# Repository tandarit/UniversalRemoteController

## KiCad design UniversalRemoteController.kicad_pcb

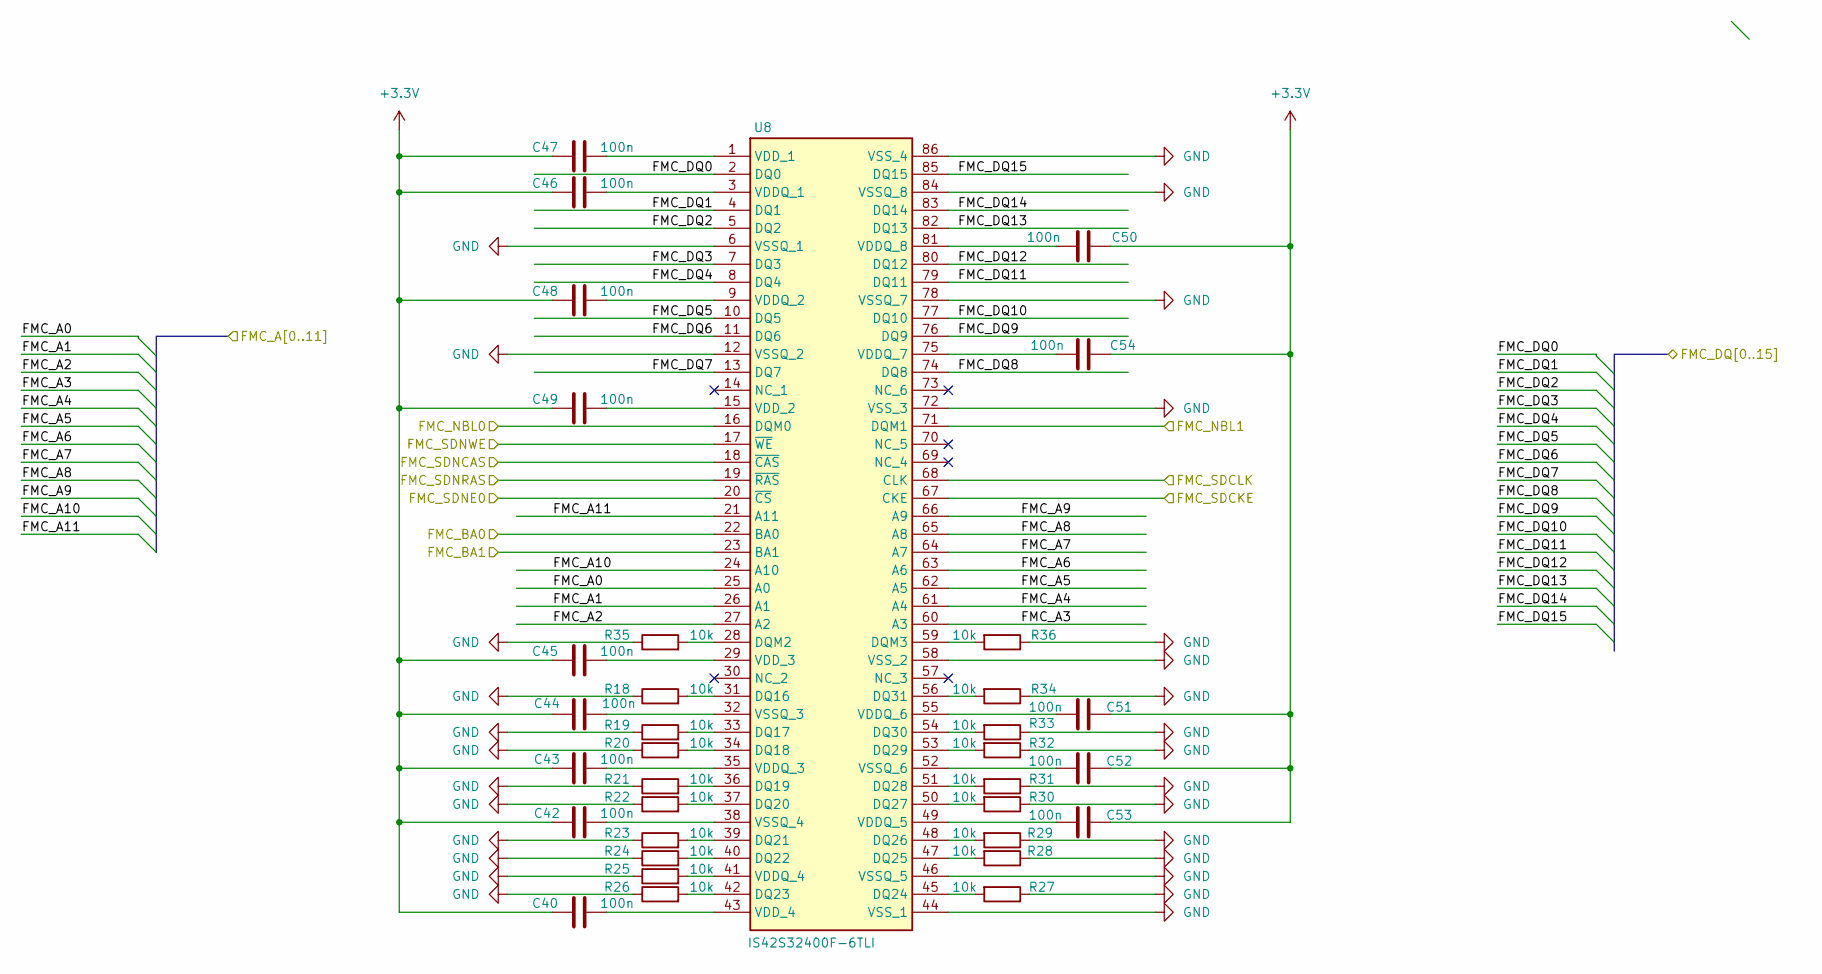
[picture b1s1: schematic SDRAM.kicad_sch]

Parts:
C40, C42, C43, C44, C45, C46, C47, C48, C49, C50, C51, C52, C53, C54: 100n; C_0402_1005Metric
R18, R19, R20, R21, R22, R23, R24, R25, R26, R27, R28, R29, R30, R31, R32, R33, R34, R35, R36: 10k; C_0402_1005Metric
U8: IS42S32400F-6TLI; SOP50P1176X120-86N; Mouser Part Number 870-IS42S32400F-6TLI

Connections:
+3.3V: C40.1, C42.1, C43.1, C44.1, C45.1, C46.1, C47.1, C48.1, C49.1, C50.1, C51.1, C52.1, C53.1, C54.1; also elsewhere on the board
/MCU/FMC_A0: U8.25 (A0); also elsewhere on the board
/MCU/FMC_A1: U8.26 (A1); also elsewhere on the board
/MCU/FMC_A2: U8.27 (A2); also elsewhere on the board
/MCU/FMC_A3: U8.60 (A3); also elsewhere on the board
/MCU/FMC_A4: U8.61 (A4); also elsewhere on the board
/MCU/FMC_A5: U8.62 (A5); also elsewhere on the board
/MCU/FMC_A6: U8.63 (A6); also elsewhere on the board
/MCU/FMC_A7: U8.64 (A7); also elsewhere on the board
/MCU/FMC_A8: U8.65 (A8); also elsewhere on the board
/MCU/FMC_A9: U8.66 (A9); also elsewhere on the board
/MCU/FMC_A10: U8.24 (A10); also elsewhere on the board
/MCU/FMC_A11: U8.21 (A11); also elsewhere on the board
/MCU/FMC_BA0: U8.22 (BA0); also elsewhere on the board
/MCU/FMC_BA1: U8.23 (BA1); also elsewhere on the board
/MCU/FMC_DQ0: U8.2 (DQ0); also elsewhere on the board
/MCU/FMC_DQ1: U8.4 (DQ1); also elsewhere on the board
/MCU/FMC_DQ2: U8.5 (DQ2); also elsewhere on the board
/MCU/FMC_DQ3: U8.7 (DQ3); also elsewhere on the board
/MCU/FMC_DQ4: U8.8 (DQ4); also elsewhere on the board
/MCU/FMC_DQ5: U8.10 (DQ5); also elsewhere on the board
/MCU/FMC_DQ6: U8.11 (DQ6); also elsewhere on the board
/MCU/FMC_DQ7: U8.13 (DQ7); also elsewhere on the board
/MCU/FMC_DQ8: U8.74 (DQ8); also elsewhere on the board
/MCU/FMC_DQ9: U8.76 (DQ9); also elsewhere on the board
/MCU/FMC_DQ10: U8.77 (DQ10); also elsewhere on the board
/MCU/FMC_DQ11: U8.79 (DQ11); also elsewhere on the board
/MCU/FMC_DQ12: U8.80 (DQ12); also elsewhere on the board
/MCU/FMC_DQ13: U8.82 (DQ13); also elsewhere on the board
/MCU/FMC_DQ14: U8.83 (DQ14); also elsewhere on the board
/MCU/FMC_DQ15: U8.85 (DQ15); also elsewhere on the board
/MCU/FMC_NBL0: U8.16 (DQM0); also elsewhere on the board
/MCU/FMC_NBL1: U8.71 (DQM1); also elsewhere on the board
/MCU/FMC_SDCKE: U8.67 (CKE); also elsewhere on the board
/MCU/FMC_SDCLK: U8.68 (CLK); also elsewhere on the board
/MCU/FMC_SDNCAS: U8.18 (~CAS); also elsewhere on the board
/MCU/FMC_SDNE0: U8.20 (~CS); also elsewhere on the board
/MCU/FMC_SDNRAS: U8.19 (~RAS); also elsewhere on the board
/MCU/FMC_SDNWE: U8.17 (~WE); also elsewhere on the board
GND: R18.1, R19.1, R20.1, R21.1, R22.1, R23.1, R24.1, R25.1, R26.1, R27.1, R28.1, R29.1, R30.1, R31.1, R32.1, R33.1, R34.1, R35.1, R36.1, U8.6 (VSSQ_1), U8.12 (VSSQ_2), U8.44 (VSS_1), U8.46 (VSSQ_5), U8.58 (VSS_2), U8.72 (VSS_3), U8.78 (VSSQ_7), U8.84 (VSSQ_8), U8.86 (VSS_4); also elsewhere on the board
unnamed: R18.2, U8.31 (DQ16)
unnamed: R19.2, U8.33 (DQ17)
unnamed: R20.2, U8.34 (DQ18)
unnamed: R21.2, U8.36 (DQ19)
unnamed: R22.2, U8.37 (DQ20)
unnamed: R23.2, U8.39 (DQ21)
unnamed: R24.2, U8.40 (DQ22)
unnamed: R26.2, U8.42 (DQ23)
unnamed: R27.2, U8.45 (DQ24)
unnamed: R28.2, U8.47 (DQ25)
unnamed: R29.2, U8.48 (DQ26)
unnamed: R30.2, U8.50 (DQ27)
unnamed: R31.2, U8.51 (DQ28)
unnamed: R32.2, U8.53 (DQ29)
unnamed: R33.2, U8.54 (DQ30)
unnamed: R34.2, U8.56 (DQ31)
unnamed: R35.2, U8.28 (DQM2)
unnamed: R36.2, U8.59 (DQM3)
unnamed: C46.2, U8.3 (VDDQ_1)
unnamed: C48.2, U8.9 (VDDQ_2)
unnamed: C43.2, U8.35 (VDDQ_3)
unnamed: R25.2, U8.41 (VDDQ_4)
unnamed: C53.2, U8.49 (VDDQ_5)
unnamed: C51.2, U8.55 (VDDQ_6)
unnamed: C54.2, U8.75 (VDDQ_7)
unnamed: C50.2, U8.81 (VDDQ_8)
unnamed: C47.2, U8.1 (VDD_1)
unnamed: C49.2, U8.15 (VDD_2)
unnamed: C45.2, U8.29 (VDD_3)
unnamed: C40.2, U8.43 (VDD_4)
unnamed: C44.2, U8.32 (VSSQ_3)
unnamed: C42.2, U8.38 (VSSQ_4)
unnamed: C52.2, U8.52 (VSSQ_6)

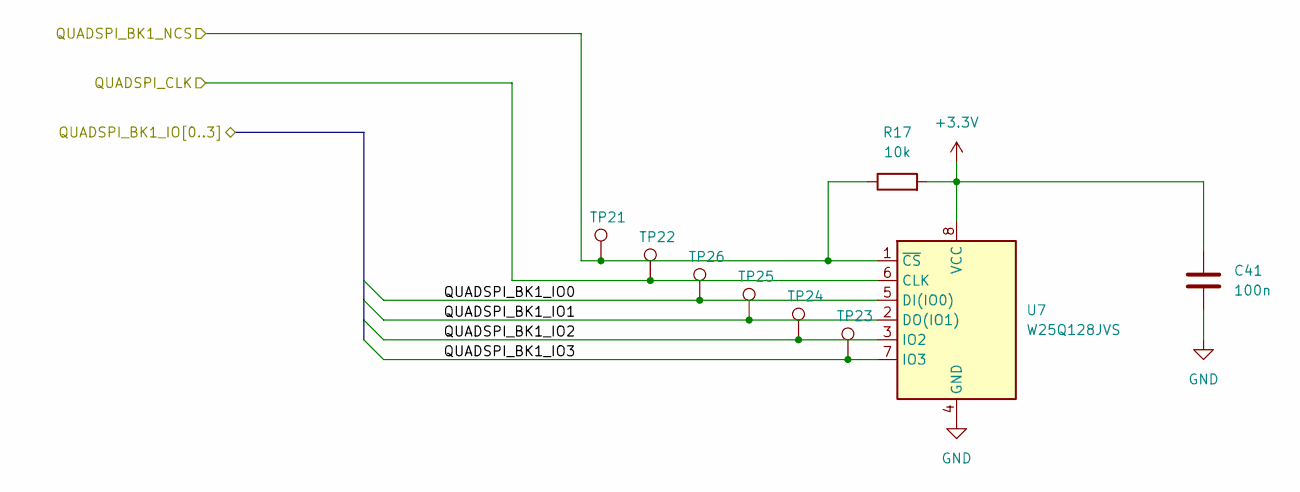
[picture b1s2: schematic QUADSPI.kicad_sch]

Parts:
C41: 100n; C_0402_1005Metric
R17: 10k; R_0402_1005Metric
TP21, TP22, TP23, TP24, TP25, TP26: TestPoint; TestPoint_Pad_D1.0mm
U7: W25Q128JVS; SOIC-8_5.23x5.23mm_P1.27mm

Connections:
+3.3V: C41.1, R17.2, U7.8 (VCC); also elsewhere on the board
/MCU/QUADSPI_BK1_IO0: TP26.1, U7.5 (DI(IO0)); also elsewhere on the board
/MCU/QUADSPI_BK1_IO1: TP25.1, U7.2 (DO(IO1)); also elsewhere on the board
/MCU/QUADSPI_BK1_IO2: TP24.1, U7.3 (IO2); also elsewhere on the board
/MCU/QUADSPI_BK1_IO3: TP23.1, U7.7 (IO3); also elsewhere on the board
/MCU/QUADSPI_BK1_NCS: TP22.1, U7.6 (CLK); also elsewhere on the board
/MCU/QUADSPI_CLK: R17.1, TP21.1, U7.1 (~CS); also elsewhere on the board
GND: C41.2, U7.4 (GND); also elsewhere on the board

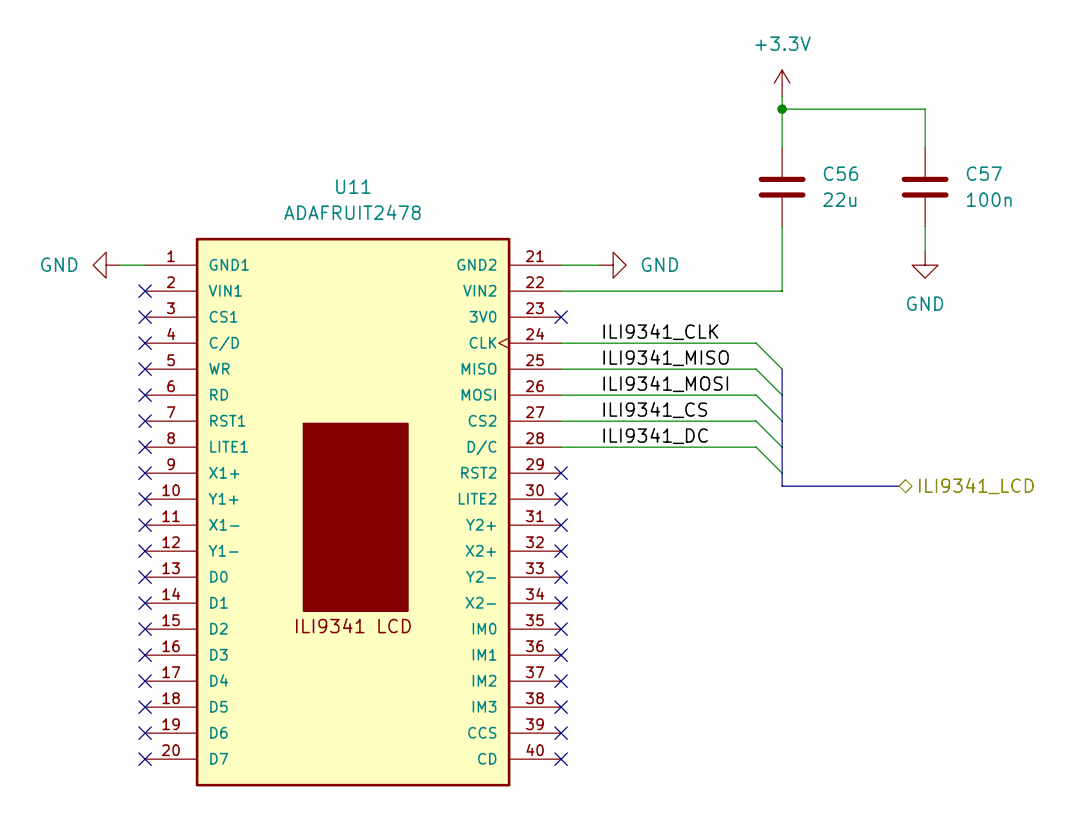
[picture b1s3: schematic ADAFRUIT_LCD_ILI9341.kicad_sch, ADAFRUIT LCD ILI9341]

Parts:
C56: 22u; C_0805_2012Metric
C57: 100n; C_0402_1005Metric
U11: ADAFRUIT2478; ADAFRUIT_2478

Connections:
+3.3V: C56.1, C57.1; also elsewhere on the board
/ADAFRUIT_LCD_ILI9341/ILI9341_CLK: U11.24 (CLK)
/ADAFRUIT_LCD_ILI9341/ILI9341_CS: U11.27 (CS2)
/ADAFRUIT_LCD_ILI9341/ILI9341_DC: U11.28 (D/C)
/ADAFRUIT_LCD_ILI9341/ILI9341_MISO: U11.25 (MISO)
/ADAFRUIT_LCD_ILI9341/ILI9341_MOSI: U11.26 (MOSI)
GND: C57.2, U11.1 (GND1), U11.21 (GND2); also elsewhere on the board
unnamed: C56.2, U11.22 (VIN2)

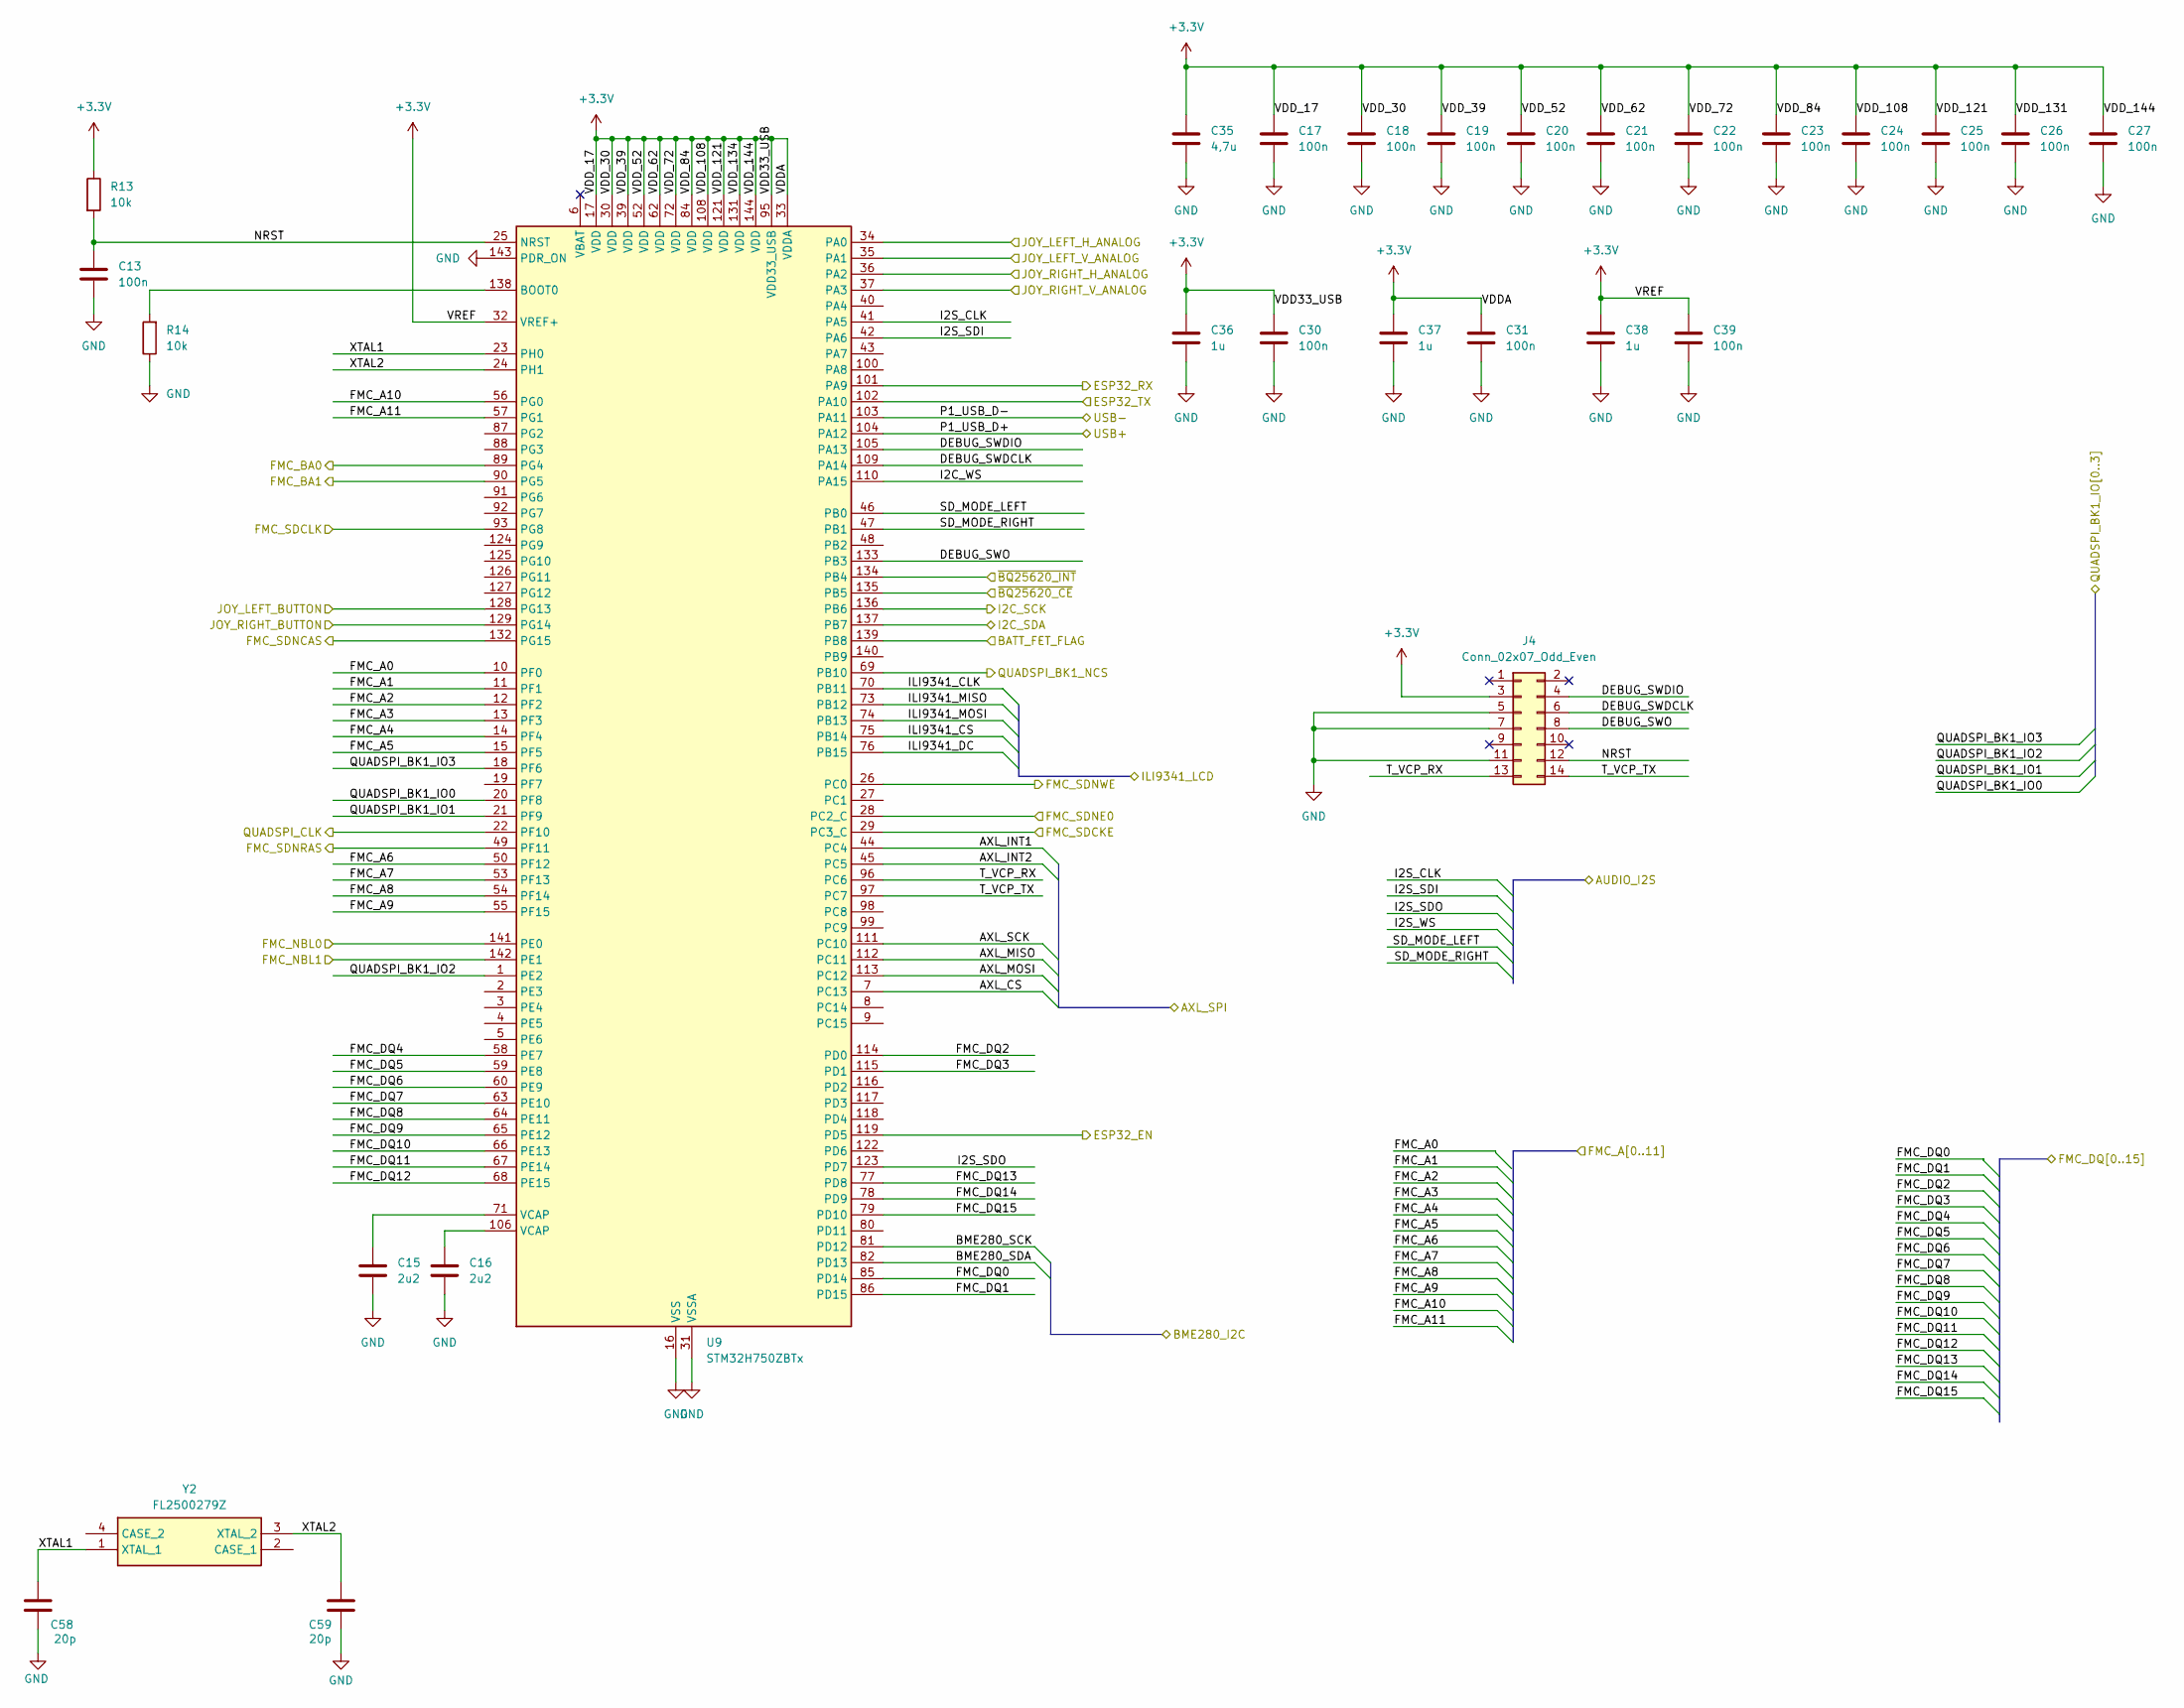
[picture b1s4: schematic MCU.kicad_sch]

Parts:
C13, C17, C18, C19, C20, C21, C22, C23, C24, C25, C26, C27, C30, C31, C39: 100n; C_0402_1005Metric
C15, C16: 2u2; C_0805_2012Metric
C35: 4,7u; C_0603_1608Metric
C36, C37, C38: 1u; C_0603_1608Metric
C58, C59: 20p; C_0402_1005Metric
J4: Conn_02x07_Odd_Even; PinHeader_2x07_P1.27mm_Vertical_SMD
R13, R14: 10k; C_0805_2012Metric
U9: STM32H750ZBTx; LQFP-144_20x20mm_P0.5mm
Y2: FL2500279Z; Mouser Part Number 729-FL2500279Z

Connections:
+3.3V: C17.1, C18.1, C19.1, C20.1, C21.1, C22.1, C23.1, C24.1, C25.1, C26.1, C27.1, C30.1, C31.1, C35.1, C36.1, C37.1, C38.1, C39.1, J4.3, R13.1, U9.17 (VDD), U9.30 (VDD), U9.32 (VREF+), U9.33 (VDDA), U9.39 (VDD), U9.52 (VDD), U9.62 (VDD), U9.72 (VDD), U9.84 (VDD), U9.95 (VDD33_USB), U9.108 (VDD), U9.121 (VDD), U9.131 (VDD), U9.144 (VDD); also elsewhere on the board
/BluetoothWiFi/ESP32_EN: U9.119 (PD5); also elsewhere on the board
/BluetoothWiFi/ESP32_RX: U9.101 (PA9); also elsewhere on the board
/BluetoothWiFi/ESP32_TX: U9.102 (PA10); also elsewhere on the board
/MCU/AXL_CS: U9.7 (PC13)
/MCU/AXL_INT1: U9.44 (PC4)
/MCU/AXL_INT2: U9.45 (PC5)
/MCU/AXL_MISO: U9.112 (PC11)
/MCU/AXL_MOSI: U9.113 (PC12)
/MCU/AXL_SCK: U9.111 (PC10)
/MCU/BATT_FET_FLAG: U9.139 (PB8); also elsewhere on the board
/MCU/BME280_SCK: U9.81 (PD12)
/MCU/BME280_SDA: U9.82 (PD13)
/MCU/DEBUG_SWDCLK: J4.6, U9.109 (PA14)
/MCU/DEBUG_SWDIO: J4.4, U9.105 (PA13)
/MCU/DEBUG_SWO: J4.8, U9.133 (PB3)
/MCU/FMC_A0: U9.10 (PF0); also elsewhere on the board
/MCU/FMC_A1: U9.11 (PF1); also elsewhere on the board
/MCU/FMC_A2: U9.12 (PF2); also elsewhere on the board
/MCU/FMC_A3: U9.13 (PF3); also elsewhere on the board
/MCU/FMC_A4: U9.14 (PF4); also elsewhere on the board
/MCU/FMC_A5: U9.15 (PF5); also elsewhere on the board
/MCU/FMC_A6: U9.50 (PF12); also elsewhere on the board
/MCU/FMC_A7: U9.53 (PF13); also elsewhere on the board
/MCU/FMC_A8: U9.54 (PF14); also elsewhere on the board
/MCU/FMC_A9: U9.55 (PF15); also elsewhere on the board
/MCU/FMC_A10: U9.56 (PG0); also elsewhere on the board
/MCU/FMC_A11: U9.57 (PG1); also elsewhere on the board
/MCU/FMC_BA0: U9.89 (PG4); also elsewhere on the board
/MCU/FMC_BA1: U9.90 (PG5); also elsewhere on the board
/MCU/FMC_DQ0: U9.85 (PD14); also elsewhere on the board
/MCU/FMC_DQ1: U9.86 (PD15); also elsewhere on the board
/MCU/FMC_DQ2: U9.114 (PD0); also elsewhere on the board
/MCU/FMC_DQ3: U9.115 (PD1); also elsewhere on the board
/MCU/FMC_DQ4: U9.58 (PE7); also elsewhere on the board
/MCU/FMC_DQ5: U9.59 (PE8); also elsewhere on the board
/MCU/FMC_DQ6: U9.60 (PE9); also elsewhere on the board
/MCU/FMC_DQ7: U9.63 (PE10); also elsewhere on the board
/MCU/FMC_DQ8: U9.64 (PE11); also elsewhere on the board
/MCU/FMC_DQ9: U9.65 (PE12); also elsewhere on the board
/MCU/FMC_DQ10: U9.66 (PE13); also elsewhere on the board
/MCU/FMC_DQ11: U9.67 (PE14); also elsewhere on the board
/MCU/FMC_DQ12: U9.68 (PE15); also elsewhere on the board
/MCU/FMC_DQ13: U9.77 (PD8); also elsewhere on the board
/MCU/FMC_DQ14: U9.78 (PD9); also elsewhere on the board
/MCU/FMC_DQ15: U9.79 (PD10); also elsewhere on the board
/MCU/FMC_NBL0: U9.141 (PE0); also elsewhere on the board
/MCU/FMC_NBL1: U9.142 (PE1); also elsewhere on the board
/MCU/FMC_SDCKE: U9.29 (PC3_C); also elsewhere on the board
/MCU/FMC_SDCLK: U9.93 (PG8); also elsewhere on the board
/MCU/FMC_SDNCAS: U9.132 (PG15); also elsewhere on the board
/MCU/FMC_SDNE0: U9.28 (PC2_C); also elsewhere on the board
/MCU/FMC_SDNRAS: U9.49 (PF11); also elsewhere on the board
/MCU/FMC_SDNWE: U9.26 (PC0); also elsewhere on the board
/MCU/I2C_SCK: U9.136 (PB6); also elsewhere on the board
/MCU/I2C_SDA: U9.137 (PB7); also elsewhere on the board
/MCU/I2C_WS: U9.110 (PA15)
/MCU/I2S_CLK: U9.41 (PA5)
/MCU/I2S_SDI: U9.42 (PA6)
/MCU/I2S_SDO: U9.123 (PD7)
/MCU/ILI9341_CLK: U9.70 (PB11)
/MCU/ILI9341_CS: U9.75 (PB14)
/MCU/ILI9341_DC: U9.76 (PB15)
/MCU/ILI9341_MISO: U9.73 (PB12)
/MCU/ILI9341_MOSI: U9.74 (PB13)
/MCU/JOY_LEFT_BUTTON: U9.128 (PG13); also elsewhere on the board
/MCU/JOY_LEFT_H_ANALOG: U9.34 (PA0); also elsewhere on the board
/MCU/JOY_LEFT_V_ANALOG: U9.35 (PA1); also elsewhere on the board
/MCU/JOY_RIGHT_BUTTON: U9.129 (PG14); also elsewhere on the board
/MCU/JOY_RIGHT_H_ANALOG: U9.36 (PA2); also elsewhere on the board
/MCU/JOY_RIGHT_V_ANALOG: U9.37 (PA3); also elsewhere on the board
/MCU/NRST: C13.1, J4.12, R13.2, U9.25 (NRST)
/MCU/P1_USB_D+: U9.104 (PA12); also elsewhere on the board
/MCU/P1_USB_D-: U9.103 (PA11); also elsewhere on the board
/MCU/QUADSPI_BK1_IO0: U9.20 (PF8); also elsewhere on the board
/MCU/QUADSPI_BK1_IO1: U9.21 (PF9); also elsewhere on the board
/MCU/QUADSPI_BK1_IO2: U9.1 (PE2); also elsewhere on the board
/MCU/QUADSPI_BK1_IO3: U9.18 (PF6); also elsewhere on the board
/MCU/QUADSPI_BK1_NCS: U9.69 (PB10); also elsewhere on the board
/MCU/QUADSPI_CLK: U9.22 (PF10); also elsewhere on the board
/MCU/SD_MODE_LEFT: U9.46 (PB0)
/MCU/SD_MODE_RIGHT: U9.47 (PB1)
/MCU/T_VCP_RX: J4.13, U9.96 (PC6)
/MCU/T_VCP_TX: J4.14, U9.97 (PC7)
/MCU/XTAL1: C58.1, U9.23 (PH0), Y2.1 (XTAL_1)
/MCU/XTAL2: C59.1, U9.24 (PH1), Y2.3 (XTAL_2)
/MCU/~BQ25620_CE: U9.135 (PB5); also elsewhere on the board
/MCU/~BQ25620_INT: U9.134 (PB4); also elsewhere on the board
GND: C13.2, C15.1, C16.1, C17.2, C18.2, C19.2, C20.2, C21.2, C22.2, C23.2, C24.2, C25.2, C26.2, C27.2, C30.2, C31.2, C35.2, C36.2, C37.2, C38.2, C39.2, C58.2, C59.2, J4.5, J4.7, J4.11, R14.1, U9.16 (VSS), U9.31 (VSSA), U9.38 (VSS), U9.51 (VSS), U9.61 (VSS), U9.83 (VSS), U9.94 (VSS), U9.107 (VSS), U9.120 (VSS), U9.130 (VSS), U9.143 (PDR_ON); also elsewhere on the board
unnamed: C15.2, U9.71 (VCAP)
unnamed: C16.2, U9.106 (VCAP)
unnamed: R14.2, U9.138 (BOOT0)

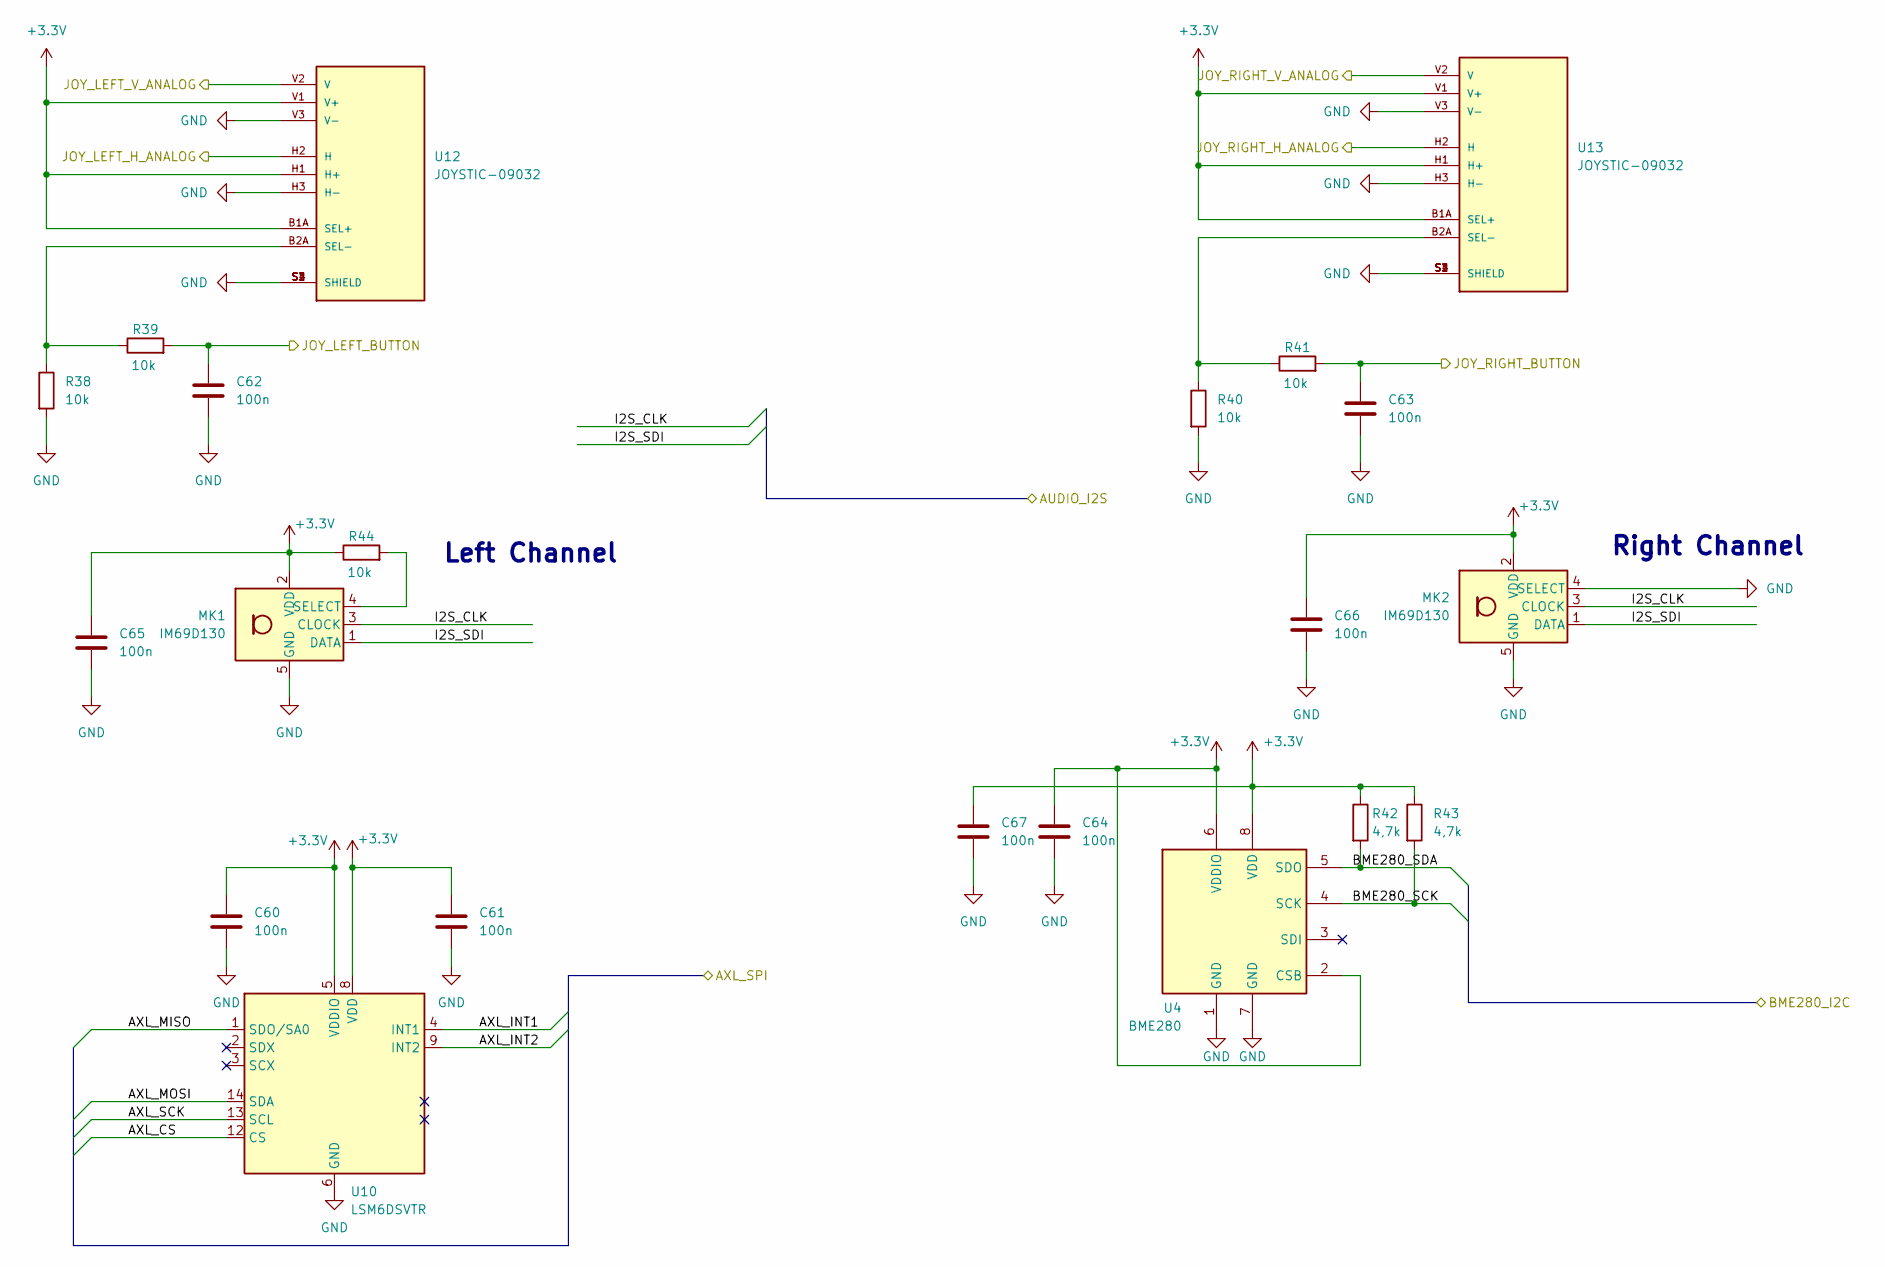
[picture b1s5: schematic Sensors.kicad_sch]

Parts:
C60, C61, C62, C63, C64, C65, C66, C67: 100n; C_0402_1005Metric
MK1, MK2: IM69D130; Infineon_PG-LLGA-5-1
R38, R39, R40, R41: 10k; C_0402_1005Metric
R42, R43: 4,7k; C_0402_1005Metric
R44: 10k; R_0402_1005Metric
U4: BME280; Bosch_LGA-8_2.5x2.5mm_P0.65mm_ClockwisePinNumbering
U10: LSM6DSVTR; LGA-14_3x2.5mm_P0.5mm_LayoutBorder3x4y
U12, U13: JOYSTIC-09032; XDCR_COM-09032; PARTREV N/A

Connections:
+3.3V: C60.1, C61.1, C64.1, C65.1, C66.1, C67.1, MK1.2 (VDD), MK2.2 (VDD), R42.1, R43.1, R44.1, U4.2 (CSB), U4.6 (VDDIO), U4.8 (VDD), U10.5 (VDDIO), U10.8 (VDD), U12.B1A (SEL+), U12.H1 (H+), U12.V1 (V+), U13.B1A (SEL+), U13.H1 (H+), U13.V1 (V+); also elsewhere on the board
/MCU/JOY_LEFT_BUTTON: C62.1, R39.2; also elsewhere on the board
/MCU/JOY_LEFT_H_ANALOG: U12.H2 (H); also elsewhere on the board
/MCU/JOY_LEFT_V_ANALOG: U12.V2 (V); also elsewhere on the board
/MCU/JOY_RIGHT_BUTTON: C63.1, R41.2; also elsewhere on the board
/MCU/JOY_RIGHT_H_ANALOG: U13.H2 (H); also elsewhere on the board
/MCU/JOY_RIGHT_V_ANALOG: U13.V2 (V); also elsewhere on the board
/Sensors/AXL_CS: U10.12 (CS)
/Sensors/AXL_INT1: U10.4 (INT1)
/Sensors/AXL_INT2: U10.9 (INT2)
/Sensors/AXL_MISO: U10.1 (SDO/SA0)
/Sensors/AXL_MOSI: U10.14 (SDA)
/Sensors/AXL_SCK: U10.13 (SCL)
/Sensors/BME280_SCK: R43.2, U4.4 (SCK)
/Sensors/BME280_SDA: R42.2, U4.5 (SDO)
/Sensors/I2S_CLK: MK1.3 (CLOCK), MK2.3 (CLOCK)
/Sensors/I2S_SDI: MK1.1 (DATA), MK2.1 (DATA)
GND: C60.2, C61.2, C62.2, C63.2, C64.2, C65.2, C66.2, C67.2, MK1.5 (GND), MK2.4 (SELECT), MK2.5 (GND), R38.2, R40.2, U4.1 (GND), U4.7 (GND), U10.6 (GND), U10.7 (GND), U12.H3 (H-), U12.S1 (SHIELD), U12.S2 (SHIELD), U12.S3 (SHIELD), U12.S4 (SHIELD), U12.V3 (V-), U13.H3 (H-), U13.S1 (SHIELD), U13.S2 (SHIELD), U13.S3 (SHIELD), U13.S4 (SHIELD), U13.V3 (V-); also elsewhere on the board
unnamed: MK1.4 (SELECT), R44.2
unnamed: R38.1, R39.1, U12.B2A (SEL-)
unnamed: R40.1, R41.1, U13.B2A (SEL-)

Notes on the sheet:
Right Channel
Left Channel

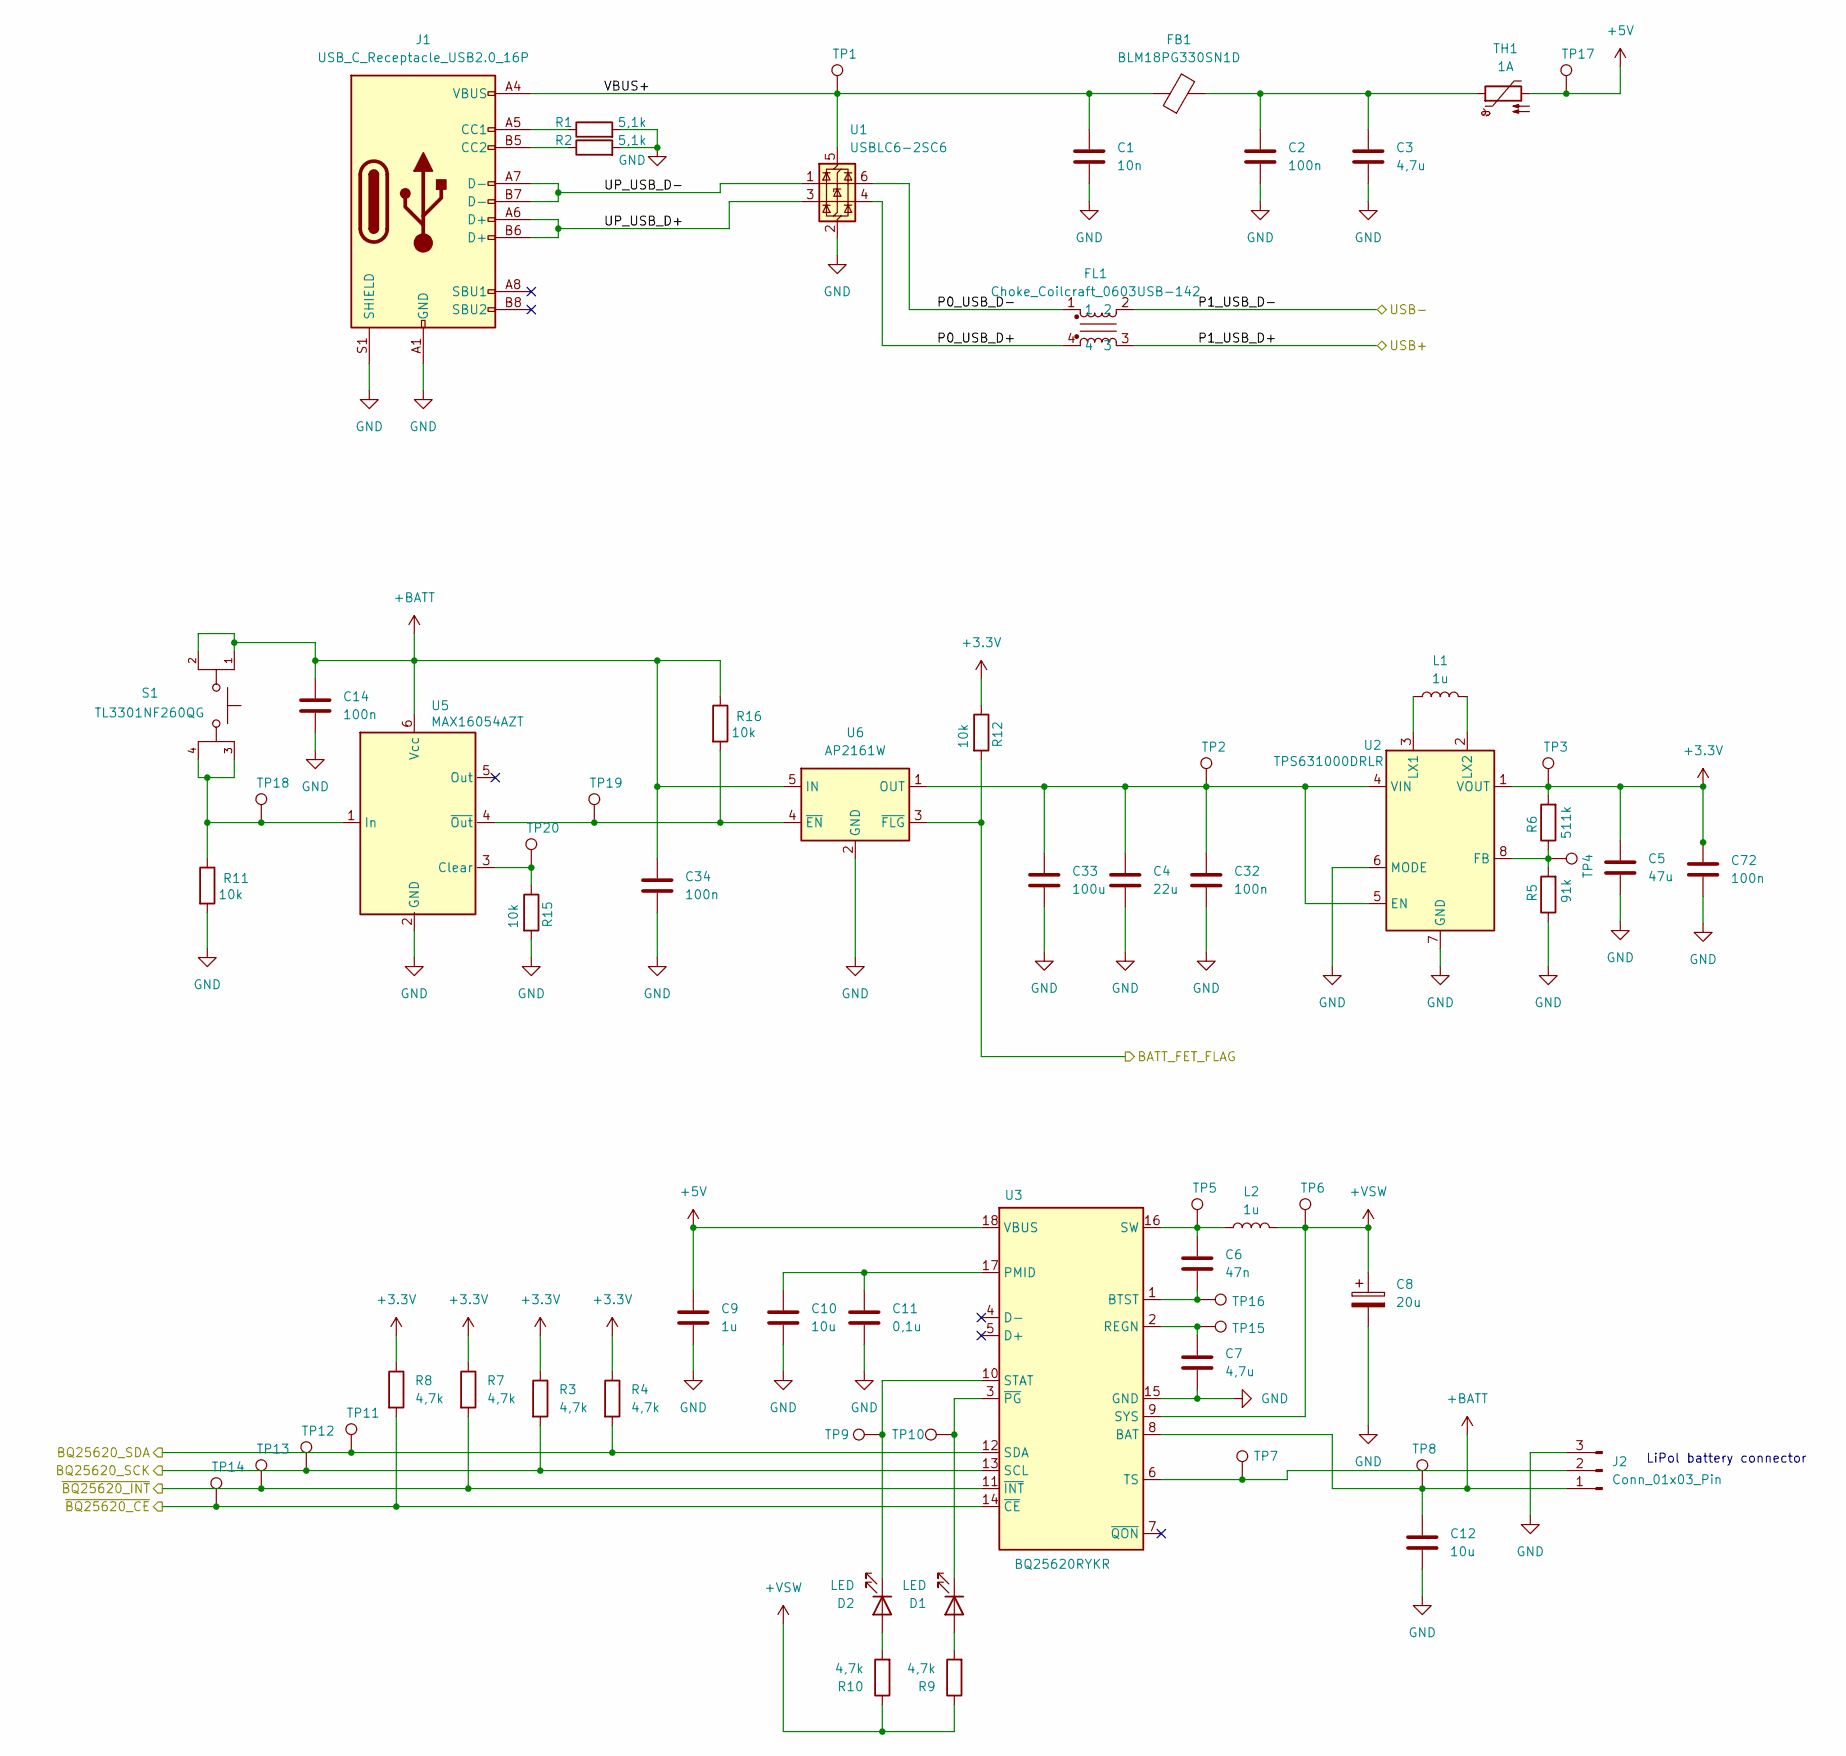
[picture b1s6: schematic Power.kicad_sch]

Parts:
C1: 10n; C_0402_1005Metric
C2, C14, C32, C34, C72: 100n; C_0402_1005Metric
C3: 4,7u; C_1206_3216Metric
C4: 22u; C_0805_2012Metric
C5: 47u; C_0805_2012Metric
C6: 47n; C_0402_1005Metric
C7: 4,7u; C_0805_2012Metric
C8: 20u; C_0805_2012Metric
C9: 1u; C_0805_2012Metric
C10, C12: 10u; C_0805_2012Metric
C11: 0,1u; C_0603_1608Metric
C33: 100u; C_1206_3216Metric
D1, D2: LED; LED_0603_1608Metric
FB1: BLM18PG330SN1D; L_0603_1608Metric
FL1: Choke_Coilcraft_0603USB-142; 0603USB142MLC
J1: USB_C_Receptacle_USB2.0_16P; USB_C_Receptacle_GCT_USB4105-xx-A_16P_TopMnt_Horizontal
J2: Conn_01x03_Pin; PinHeader_1x03_P2.00mm_Horizontal
L1, L2: 1u; L_1008_2520Metric
R1, R2: 5,1k; R_0402_1005Metric
R3, R4, R7, R8, R9, R10: 4,7k; C_0402_1005Metric
R5: 91k; R_0603_1608Metric
R6: 511k; R_0603_1608Metric
R11, R12, R15, R16: 10k; R_01005_0402Metric
S1: TL3301NF260QG; SW_TL3301NF260QG; PARTREV E
TH1: 1A; R_0402_1005Metric
TP1, TP2, TP3, TP4, TP5, TP6, TP7, TP8, TP9, TP10, TP11, TP12, TP13, TP14, TP15, TP16, TP17, TP18, TP19, TP20: TestPoint; TestPoint_Pad_D1.0mm
U1: USBLC6-2SC6; SOT-23-6
U2: TPS631000DRLR; SOTFL50P160X60-8N
U3: BQ25620RYKR
U5: MAX16054AZT; SOT-23-6
U6: AP2161W; SOT-23-5

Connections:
+3.3V: C5.1, C72.1, R3.1, R4.1, R6.2, R7.1, R8.1, R12.1, TP3.1, U2.1 (VOUT); also elsewhere on the board
+5V: C9.1, TH1.2, TP17.1, U3.18 (VBUS)
+BATT: C12.1, C14.1, C34.1, J2.1, R16.1, S1.1, S1.2, TP8.1, U3.8 (BAT), U5.6 (Vcc), U6.5 (IN)
+VSW: C8.1, L2.2, R9.1, R10.1, TP6.1, U3.9 (SYS)
/MCU/BATT_FET_FLAG: R12.2, U6.3 (~FLG); also elsewhere on the board
/MCU/I2C_SCK: R3.2, TP12.1, U3.13 (SCL); also elsewhere on the board
/MCU/I2C_SDA: R4.2, TP11.1, U3.12 (SDA); also elsewhere on the board
/MCU/P1_USB_D+: FL1.3; also elsewhere on the board
/MCU/P1_USB_D-: FL1.2; also elsewhere on the board
/MCU/~BQ25620_CE: R8.2, TP14.1, U3.14 (~CE); also elsewhere on the board
/MCU/~BQ25620_INT: R7.2, TP13.1, U3.11 (~INT); also elsewhere on the board
/Power/P0_USB_D+: FL1.4, U1.4 (I/O2)
/Power/P0_USB_D-: FL1.1, U1.6 (I/O1)
/Power/UP_USB_D+: J1.A6 (D+), J1.B6 (D+), U1.3 (I/O2)
/Power/UP_USB_D-: J1.A7 (D-), J1.B7 (D-), U1.1 (I/O1)
/Power/VBUS+: C1.1, FB1.1, J1.A4 (VBUS), J1.A9 (VBUS), J1.B4 (VBUS), J1.B9 (VBUS), TP1.1, U1.5 (VBUS)
GND: C1.2, C2.2, C3.2, C4.2, C5.2, C7.2, C8.2, C9.2, C10.2, C11.2, C12.2, C14.2, C32.2, C33.2, C34.2, C72.2, J1.A1 (GND), J1.A12 (GND), J1.B1 (GND), J1.B12 (GND), J1.S1 (SHIELD), J2.3, R1.2, R2.2, R5.1, R11.2, R15.2, U1.2 (GND), U2.6 (MODE), U2.7 (GND), U3.15 (GND), U5.2 (GND), U6.2 (GND); also elsewhere on the board
unnamed: C2.1, C3.1, FB1.2, TH1.1
unnamed: D1.2 (A), R9.2
unnamed: D1.1 (K), TP10.1, U3.3 (~PG)
unnamed: D2.2 (A), R10.2
unnamed: D2.1 (K), TP9.1, U3.10 (STAT)
unnamed: J1.A5 (CC1), R1.1
unnamed: J1.B5 (CC2), R2.1
unnamed: J2.2, TP7.1, U3.6 (TS)
unnamed: C4.1, C32.1, C33.1, TP2.1, U2.4 (VIN), U2.5 (EN), U6.1 (OUT)
unnamed: R5.2, R6.1, TP4.1, U2.8 (FB)
unnamed: L1.1, U2.3 (LX1)
unnamed: L1.2, U2.2 (LX2)
unnamed: C6.2, TP16.1, U3.1 (BTST)
unnamed: C10.1, C11.1, U3.17 (PMID)
unnamed: C7.1, TP15.1, U3.2 (REGN)
unnamed: C6.1, L2.1, TP5.1, U3.16 (SW)
unnamed: R15.1, TP20.1, U5.3 (Clear)
unnamed: R11.1, S1.3, S1.4, TP18.1, U5.1 (In)
unnamed: R16.2, TP19.1, U5.4 (~Out), U6.4 (~EN)

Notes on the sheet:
LiPol battery connector
